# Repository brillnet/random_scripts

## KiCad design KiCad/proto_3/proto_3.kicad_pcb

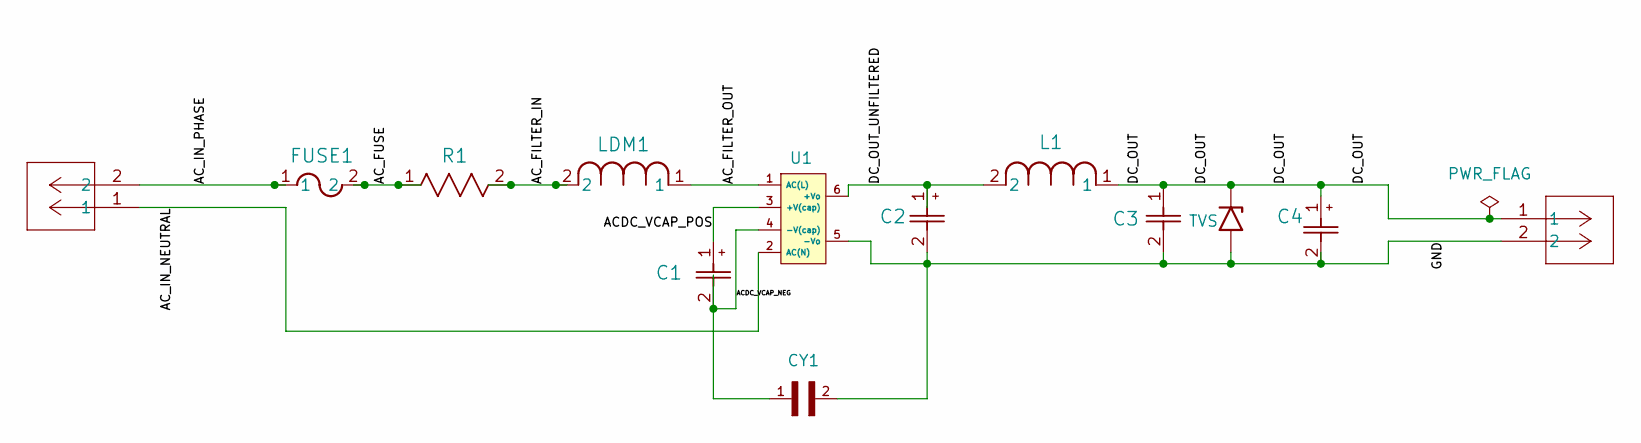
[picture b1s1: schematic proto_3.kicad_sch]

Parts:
C1: UFW1C471MPD; CAP_BX_10x20_RUB
C2: CAP_RHT_8X11P5_NCH
C3: 35ZLJ100M6.3X11; CAP_6.3X11_RUB
C4: CAP_UEP_5X11_NCH
CY1: DE2E3SA102MN3AY02F; CAP_DE2E3SA102MN3AY02F
D1: TVS; TVS_DIODE_NEW
FUSE1: FUSE_36911_LTF
J1, J2: 1729128; CONN_1729128_PXC
L1: IND_RLB9012-4R7ML
LDM1: AIUR-06_ABR
R1: res2_1-1625892-1_TEC
U1: transformer_MPL-05SC-F_new

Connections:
/ACDC_VCAP_NEG: C1.2, CY1.1, U1.4 (-V(cap))
/ACDC_VCAP_POS: C1.1, U1.3 (+V(cap))
/AC_FILTER_IN: LDM1.2, R1.2
/AC_FILTER_OUT: LDM1.1, U1.1 (AC(L))
/AC_FUSE: FUSE1.2, R1.1
/AC_IN_NEUTRAL: J2.1, U1.2 (AC(N))
/AC_IN_PHASE: FUSE1.1, J2.2
/DC_OUT: C3.1, C4.1, D1.1 (A1), J1.1, L1.1
/DC_OUT_UNFILTERED: C2.1, L1.2, U1.6 (+Vo)
/GND: C2.2, C3.2, C4.2, CY1.2, D1.2 (A2), J1.2, U1.5 (-Vo)

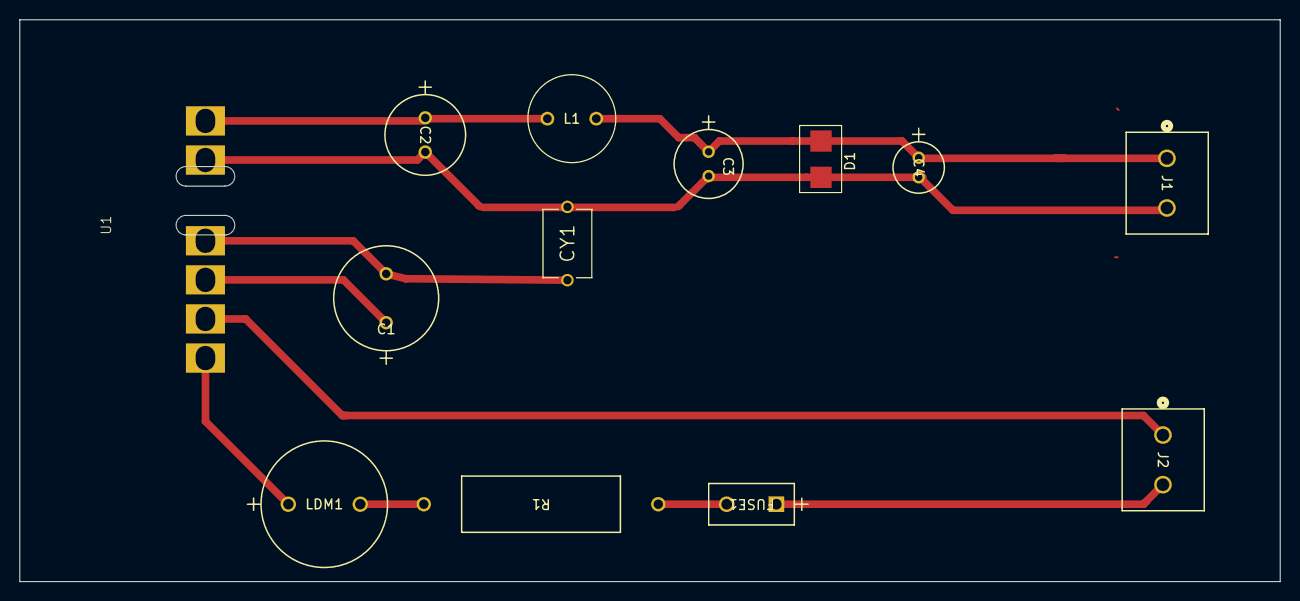
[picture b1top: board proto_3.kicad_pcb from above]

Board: 2 copper layers, 129.0 x 57.5 mm, 13 parts (0 on the bottom side), 10 nets.

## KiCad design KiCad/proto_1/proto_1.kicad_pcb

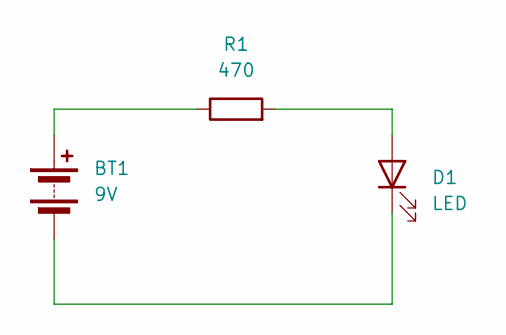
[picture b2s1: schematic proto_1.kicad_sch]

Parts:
BT1: 9V; PinHeader_2x01_P2.54mm_Vertical
D1: LED; LED_D5.0mm
R1: 470; R_Axial_DIN0614_L14.3mm_D5.7mm_P20.32mm_Horizontal

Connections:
unnamed: BT1.1 (+), R1.1
unnamed: BT1.2 (-), D1.1 (K)
unnamed: D1.2 (A), R1.2

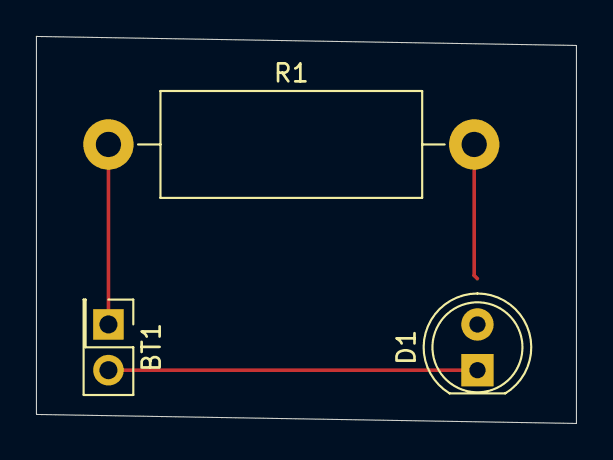
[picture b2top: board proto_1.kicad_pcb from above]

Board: 2 copper layers, 30.0 x 21.5 mm, 3 parts (0 on the bottom side), 3 nets.

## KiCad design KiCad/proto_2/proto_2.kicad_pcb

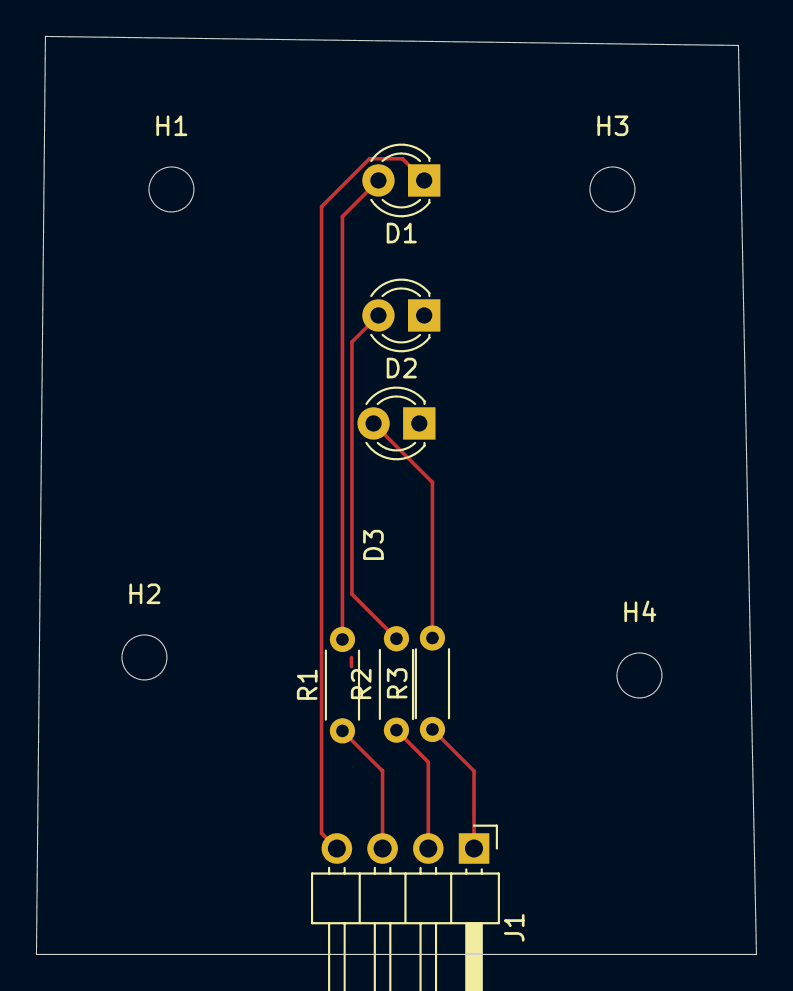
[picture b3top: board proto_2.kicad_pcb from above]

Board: 2 copper layers, 40.0 x 51.0 mm, 11 parts (0 on the bottom side), 7 nets.

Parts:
D1, D2, D3: LED; LED_D3.0mm
H1, H2, H3, H4: MountingHole; MountingHole_2.5mm
J1: Conn_01x04; PinHeader_1x04_P2.54mm_Horizontal
R1, R2, R3: R; R_Axial_DIN0204_L3.6mm_D1.6mm_P5.08mm_Horizontal

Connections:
unnamed: D1.2 (A), R1.2
unnamed: D1.1 (K), D2.1 (K), D3.1 (K), J1.4
unnamed: D2.2 (A), R2.2
unnamed: D3.2 (A), R3.2
unnamed: J1.1, R3.1
unnamed: J1.2, R2.1
unnamed: J1.3, R1.1

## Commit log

2024-02-16 Moving things around and adding go project
2024-02-16 Delete go/booking_app directory
    removing directory. not needed.
2024-02-16 Delete go/booking_app directory
    Directory not needed
2024-02-16 added gitignore, modified main with map
2024-02-18 storing user data in map
2024-02-18 Putting user data into struct
2024-02-18 added struct to store user data
2024-02-19 Added sendTicket function that starts in new thread
2024-02-20 Adding wait groups
2024-02-20 Adding palo alto lab configs
2024-02-20 removed palo lab directories for now
2024-02-20 Delete Palo-Alto directory
    Delete Palo-Alto directory
2024-02-21 adding palo-alto lab configurations
2024-02-21 bit shifting, boolean operators
2024-02-23 Arrays
2024-02-23 Adding exercise61
2024-02-23 work on exercise61
2024-02-25 finished exercise61
2024-02-25 removed some comments
2024-02-25 Removing if statement
2024-02-25 go sample webapp test
2024-02-26 exercise61 practice
2024-02-27 more work on exercise62
2024-02-29 trying slices of original string, increasing index used in for loop by substring length
2024-02-29 More work on exercise62. Need to figure out way to get this to run faster.
2024-03-02 Working on exercise63
2024-03-02 removing hard coded value of 3 and replacing with k variable"
2024-03-02 removing sets from exercise63, need ordered list, trying dict.fromkeys()
2024-03-04 Adding ldap,phpadmin and fluentd to docker compose file. Fluentd will be used to get parsed log data from the ldap container to the palo alto user id api
2024-03-04 exercise64
2024-03-05 work on exercise 64
2024-03-06 setting up ldap logging in fluentd. These logs will be sent to the palo alto api for user-id tagging.
2024-03-07 adding http output plugin
2024-03-07 fixing regex
2024-03-08 Adding user-id and api user to config.
2024-03-12 work on exercise 65
2024-03-12 more work on exercise65
2024-03-13 exercise66
2024-03-13 exercise66 is not commiting
2024-03-14 work on exercise67
2024-03-14 updates to exercise67
2024-03-15 More work on exercise67, need to deal with in the html code
2024-03-16 changes to regex in multiline parser for the ldap logs
2024-03-16 regex for ldap parsing
2024-03-16 file not needed
    file not needed
2024-03-16 adding exec section to file-fluent.conf file
2024-03-16 script to call user-id api on palo
2024-03-17 fluentd integration into palo alto lab
2024-03-17 removing includes from fluent.conf file
2024-03-18 starting work on ldap package installs on ubuntu desktop machine
2024-03-19 changing ldap configuration files
2024-03-19 Added common-session,common-password and nsswitch.conf files
2024-03-20 added docker install
2024-03-20 Adding docker repo and installation of docker packages on webserver
2024-03-20 stopping httpd service
2024-03-20 changed permissions on ldap files, changed common-password,session and nsswitch.conf files
2024-03-20 Added ldap docker container
2024-03-20 changed indenting on docker container
2024-03-21 added python3 intepreter for webserver host to docker module to work correctly
2024-03-22 added while loop inside of main loop to deal with lines contained in comment start and end tags
2024-03-22 added python3 interpreter for checking status of docker containers. Added installation epel repo and python3 to webserver
2024-03-24 pushing again
2024-03-24 fixing adding ldap and phpldapadmin to docker compose file
2024-03-24 Added root user to Dockerfile
2024-03-24 Removing ldap and phpadmin containers from playbook.yaml file
2024-03-24 Adding comment to start ldap,fluentd and phpadmin containers
2024-03-25 added ansible.cfg to remove host key checking and stopped apache on webserver before starting all containers
2024-03-25 Added necessary ldap files and changed playbook.yaml and added move of ldap.secret file
2024-03-25 changed phpldapadmin imagine
2024-03-25 changing linking
2024-03-26 Removed quotes from environmental variables in ldap container
2024-03-26 added local logging to ldap container
2024-03-26 changing logging driver to syslog on ldap container
2024-03-26 working on regex for openldap login event
2024-03-27 changing the log mounted location of syslog file in ldap logging pipeline
2024-03-27 work on full login ldap regex
2024-03-29 Fixing/Adding regex for login event in fluentd.conf
2024-03-29 added username and group to output
2024-03-29 work on script to talk to palo alto api
2024-03-29 Added pip3 and python requests to Dockerfile for fluentd container
2024-03-29 Adding update and no-cache line to the pip3 install in the Dockerfile
2024-03-30 python instead of python3 in fluent.conf file
2024-03-30 changing script used in fluent.conf file working on user_id_update.py script
2024-03-31 cleaning up palo alto post script, adding sample flask app to test with
2024-04-01 cleaning up user_id_post script
2024-04-01 removing file-fluent.conf
2024-04-02 Added any number of spaces ater month in log line.
2024-04-02 adding message log
2024-04-02 shortening regular expressions in fluent.conf
2024-04-02 adding \n to regex in format1 line
2024-04-04 removed key from user_id_post.py script and added regex's back to fluent.conf file
2024-04-04 removed for loop from user_post.py
2024-04-04 removing old scripts
2024-04-04 removing misc directory
2024-04-04 removed old script
2024-04-07 second go exercise. status checker
2024-04-09 eBPF practice
2024-04-09 changed domain and added ou to regexs
2024-04-10 more BPF
2024-04-10 changing domain name in docker compose file
2024-04-10 added ldap.pcap
2024-04-12 eBPF. Need to add comments to test4h.py
2024-04-12 added ldap captures
2024-04-12 adding posix pcap
2024-04-12 added posix_ldap2.pcap
2024-04-14 chapter 3 exercise
2024-04-15 adding no_group pcap
2024-04-16 chaning filename
2024-04-17 4-16 config
2024-04-19 chapter 3 practice
2024-04-21 chapter 4 exercise
2024-05-01 simple c exercise
2024-05-02 Added ipsec tunnel ansible script and put udser-id_ldap work in its own folder
2024-05-02 Delete palo-alto/ansible_scripts/files directory
    Delete palo-alto/ansible_scripts/files directory
2024-05-02 Delete palo-alto/ansible_scripts/playbook.yaml
    Delete palo-alto/ansible_scripts/playbook.yaml
2024-05-02 Delete palo-alto/ansible_scripts/inventory.ini
    Delete palo-alto/ansible_scripts/inventory.ini
2024-05-02 Delete palo-alto/ansible_scripts/ansible.cfg
    Delete palo-alto/ansible_scripts/ansible.cfg
2024-05-03 exercise3
2024-05-03 exercise4
2024-05-03 changing comments
2024-05-04 exercise5
2024-05-04 exercise6
2024-05-04 changed comment for old_a
2024-05-05 Added connection.conf as template so variables can be used in it
2024-05-05 added template to be used for the ipsec.conf file
2024-05-05 removing files/connections.conf
2024-05-05 c exercise8
2024-05-06 added template for connections.secrets
2024-05-06 c exercise9
2024-05-07 c exercise10
2024-05-08 c exercise11
2024-05-09 c exercise11 more
2024-05-11 c exercise11 - more work
2024-05-12 c exercise11 fixing output
2024-05-14 c exercise12
2024-05-14 xml config for vm
2024-05-15 palo_5-15.xml
2024-05-16 restarting ipsec service
2024-05-17 changed ike variable in connections.conf
2024-05-18 added connections.secrets file to templates directory
2024-05-18 removing connections.secrets in files directory
2024-05-21 c exercise12 more work
2024-06-07 c exercise13
2024-07-03 exercise74 - interesting trick to make things go faster. converting lists to dictionaries..
2024-07-06 started work minion. put totals in individual dictionaries to make things go faster.
2024-07-06 Added total to both dictionaries
2024-07-07 removed the sum of values and adding the total lookup.
2024-08-27 exercise15
2024-08-31 exercise17
2024-09-06 chapter8 sample
2024-09-07 Added is_https_traffic function
2024-09-08 returning value of destination port in tcphdr from is_httpd_traffic
2024-09-09 removing arpanet import using using bpf_ntoh function instead of ntoh that was in arpanet library
2024-09-09 using tcp instead of tcphdr to access destination port 443
2024-09-10 more changes
2024-09-10 more work. python script not grabbing packets fastest enough
2024-09-12 dropping inbound traffic to port 443. note: xdp can only look at egress traffic
2024-09-12 removing function call in bpf trace
2024-09-13 added ingress/egress test script - ref: https://docs.pyroute2.org/iproute.html
2024-09-13 added idx to clsact add instead of hardcoded 2
2024-10-09 c - exercise19
2024-10-10 added exercise19
2024-10-10 c exercise20
2024-10-13 c exercise22
2024-10-14 c - exercise23
2024-10-14 c - exercise23 - fixing comment
2024-10-18 c - exercise24 - arrays of pointers
2024-10-20 c - exercise25
2024-10-20 c - exercise25 c file
2024-11-08 c - exercise26 - fix segmentation error
2024-11-10 c - exercise26 returning struct pointer with memory carved out from make_structure function
2025-01-28 LTSpice homework
2025-01-30 decay voltage sim using arbitrary voltage source
2025-02-04 linear test 2. Adding correct inductance values
2025-02-06 changed resistor to 5ohms
2025-02-12 changed transformer to step down to 12V, added different diodes, added 1000uF capacitor
2025-02-16 added capacitors, voltage regulator.
2025-02-18 exercise78
2025-03-30 voltage regular added
2025-04-04 adding started of switched psu schematic
2025-04-04 removing directories no longer needed
2025-04-04 removing directories
2025-04-12 first section of switched power supply. Need to add voltage feedback for regulator IC.
2025-04-12 added section of feedback circuit
2025-04-14 switched_psu test
2025-04-17 made changes to switched_psu
2025-04-19 removed DC conversion
2025-05-06 Adding KiCad folder
2025-05-06 proto2
2025-05-07 more work on proto2
2025-05-08 started reference circuit
2025-05-09 more work on proto3
2025-05-11 added more footprints to reference circuit
2025-05-12 changing symbols and footprints
2025-05-13 work on footprint and symbol for converter
2025-05-14 added power symbol, started work on pcb component placement
2025-05-15 added 3d components to footprints
2025-05-15 added transformer step file
2025-05-19 Added through-holes for 120v source, moved components around on pcb
2025-05-23 Started work on footprint for new transformer
2025-05-24 Added new transformer footprint
2025-05-24 removed footprint
2025-05-25 Changed transformer footprint, moved components on pcb
2025-05-25 removed zips, added screw terminals, updated pcb layout
2025-05-27 added correct tvs diode
2025-05-28 removed 9A diode added 7A
2025-05-29 added 1x4 screw terminal for input and output voltage rails
2025-05-30 added tvs diode and 4 port screw down block to schematic
2025-05-30 KiCad/proto_1/proto_2/proto_3/proto_3.kicad_pcb
2025-06-01 Added correct LDM inductor, footprint and symbol
2025-06-08 Added correct TVS diode footprint with correct polarities.
2025-06-09 Moving folders around
2025-06-15 Added mounting holes and ground pour
2025-06-16 seperated AC input and DC output, removed mounting holes
2025-06-17 Added power symbols, moved ground to output rail
2025-06-18 removed AC markings on L and N lines on AC input. Added individual L and P symbols to AC input lines. Need to create nets for each.
2025-06-19 labeled nets and netclasses for organization
2025-06-19 gathering news headlines script
2025-06-19 re-added ground plane
2025-06-22 added certs directory
2025-06-23 Added appropriate holes on transformer pins on edge cuts layer
2025-06-23 more wireless topics
2025-06-24 Added new footprint for transformer to pcb
2025-06-24 removing script
2025-06-25 more wireless,enterprise architecture
2025-06-25 moved traces around, added ground pour again
2025-06-26 changed space between traces on high voltage rail
2025-06-28 added step files back to footprints, moved traces around
2025-06-28 added sd-access and sd-wan things, created folders
2025-07-03 added more to ENTERPRISE_ARCHITECTURE
2026-01-18 proto1 mold
2026-02-08 more work on proto1 mold
2026-04-15 solutions architect notes
2026-04-15 EBS notes
2026-05-03 placement group notes
2026-05-05 more notes
2026-06-05 blender work
